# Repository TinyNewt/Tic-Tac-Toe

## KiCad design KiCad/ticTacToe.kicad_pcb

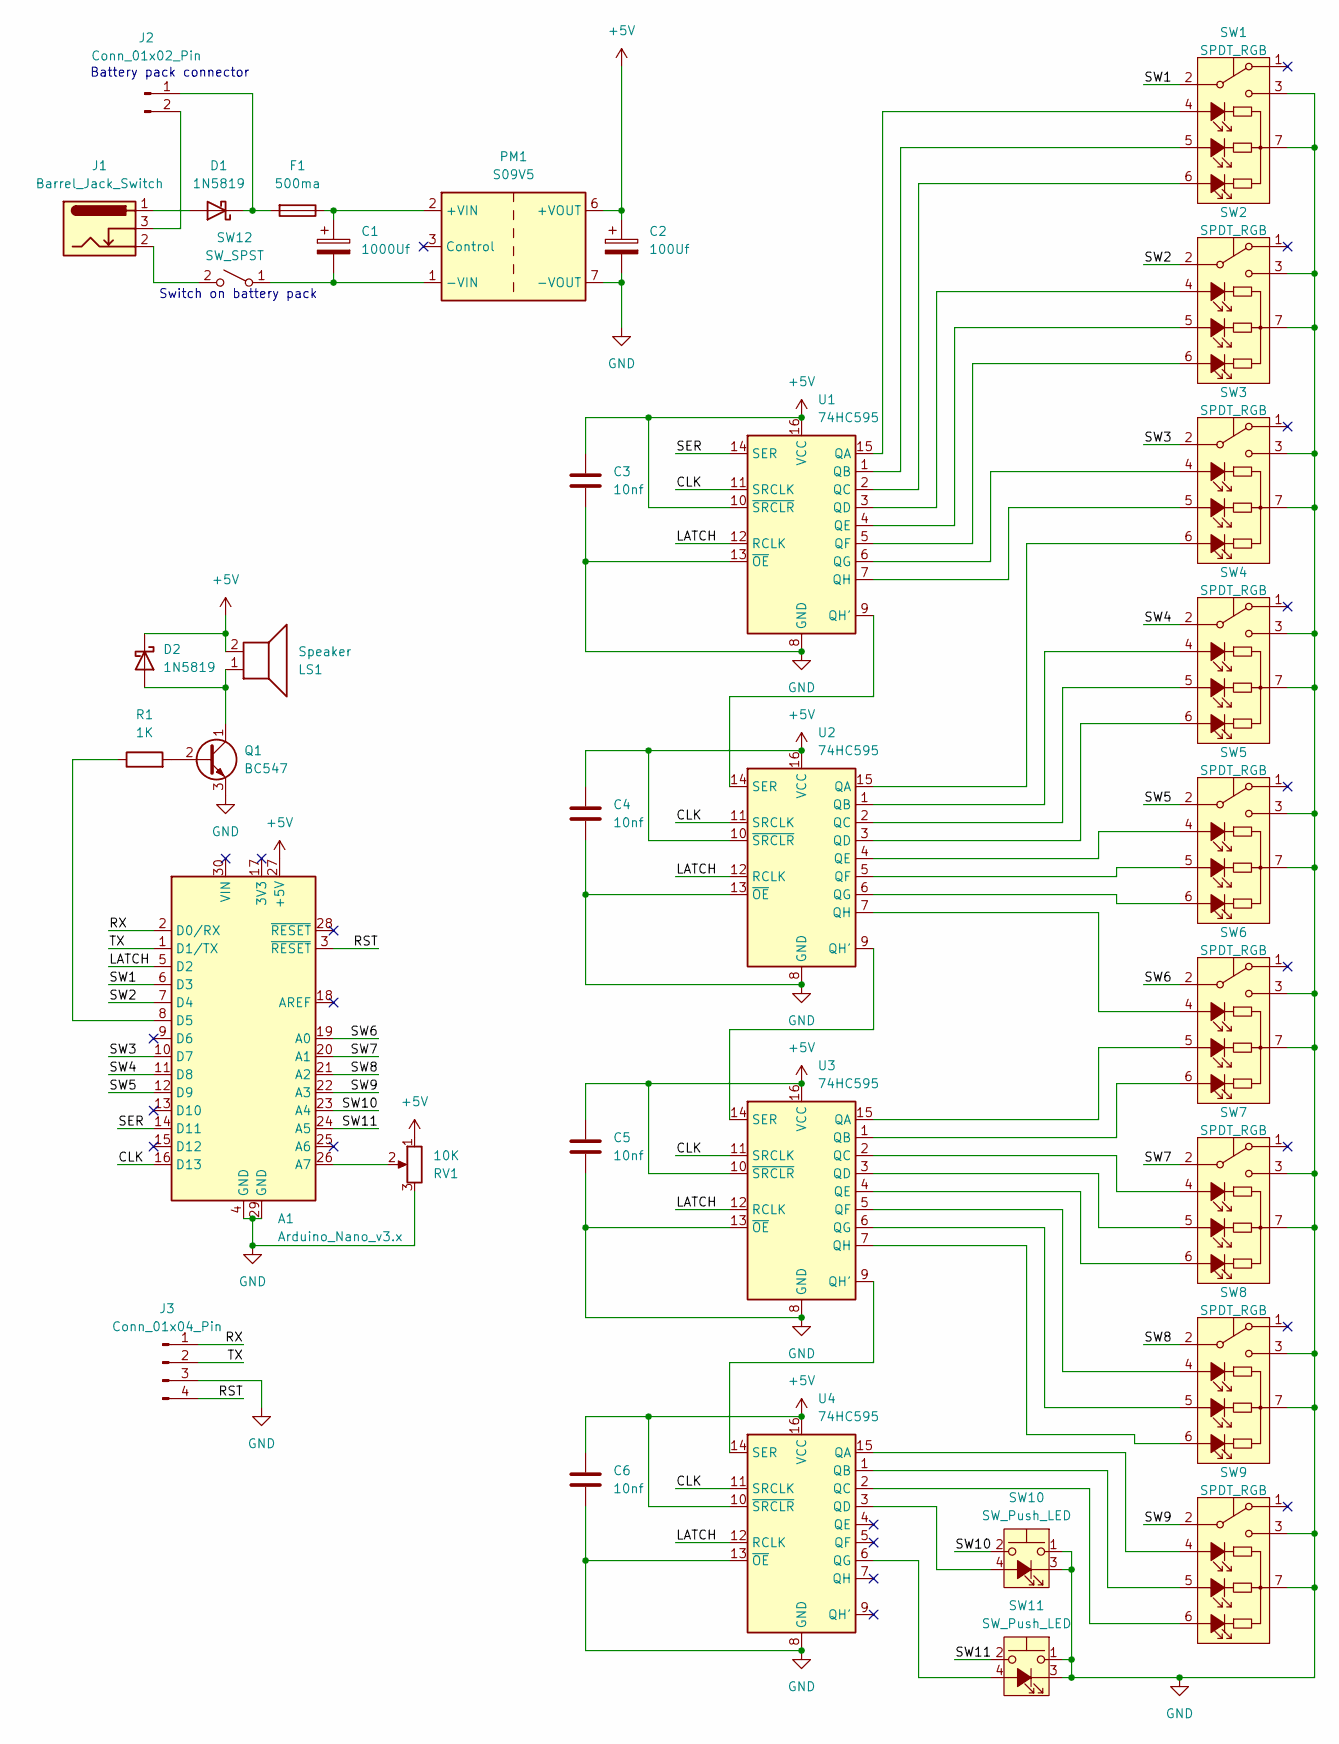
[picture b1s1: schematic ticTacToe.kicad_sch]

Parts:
A1: Arduino_Nano_v3.x; Arduino_Nano
C1: 1000Uf; CP_Radial_D8.0mm_P5.00mm; JLCPCB C10752
C2: 100Uf; CP_Radial_D8.0mm_P3.50mm; LCSC C2749
C3, C4, C5, C6: 10nf; C_Disc_D5.0mm_W2.5mm_P5.00mm
D1, D2: 1N5819; D_DO-41_SOD81_P7.62mm_Horizontal
F1: 500ma; PinHeader_1x02_P2.54mm_Vertical
J1: Barrel_Jack_Switch; BarrelJack_Horizontal
J2: Conn_01x02_Pin; PinHeader_1x02_P2.54mm_Vertical
J3: Conn_01x04_Pin; PinHeader_1x04_P2.54mm_Vertical
LS1: Speaker; PinHeader_1x02_P2.54mm_Vertical
PM1: S09V5; S09
Q1: BC547; TO-92_Inline_Wide
R1: 1K; R_Axial_DIN0204_L3.6mm_D1.6mm_P7.62mm_Horizontal
RV1: 10K; Potentiometer_Alps_RK163_Single_Horizontal
SW1, SW2, SW3, SW4, SW5, SW6, SW7, SW8, SW9: SPDT_RGB; SPDT_RGB_D19
SW10, SW11: SW_Push_LED; PinHeader_1x04_P2.54mm_Vertical
SW12: SW_SPST; PinHeader_1x02_P2.54mm_Vertical
U1, U2, U3, U4: 74HC595; DIP-16_W7.62mm_LongPads

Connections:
+5V: A1.27 (+5V), C2.1, C3.1, C4.1, C5.1, C6.1, D2.1 (K), LS1.2, PM1.6 (+VOUT), RV1.1, U1.10 (~SRCLR), U1.16 (VCC), U2.10 (~SRCLR), U2.16 (VCC), U3.10 (~SRCLR), U3.16 (VCC), U4.10 (~SRCLR), U4.16 (VCC)
/CLK: A1.16 (D13), U1.11 (SRCLK), U2.11 (SRCLK), U3.11 (SRCLK), U4.11 (SRCLK)
/LATCH: A1.5 (D2), U1.12 (RCLK), U2.12 (RCLK), U3.12 (RCLK), U4.12 (RCLK)
/RST: A1.3 (~RESET), J3.4
/RX: A1.2 (D0/RX), J3.1
/SER: A1.14 (D11), U1.14 (SER)
/SW1: A1.6 (D3), SW1.2 (B)
/SW2: A1.7 (D4), SW2.2 (B)
/SW3: A1.10 (D7), SW3.2 (B)
/SW4: A1.11 (D8), SW4.2 (B)
/SW5: A1.12 (D9), SW5.2 (B)
/SW6: A1.19 (A0), SW6.2 (B)
/SW7: A1.20 (A1), SW7.2 (B)
/SW8: A1.21 (A2), SW8.2 (B)
/SW9: A1.22 (A3), SW9.2 (B)
/SW10: A1.23 (A4), SW10.2
/SW11: A1.24 (A5), SW11.2
/TX: A1.1 (D1/TX), J3.2
GND: A1.4 (GND), A1.29 (GND), C2.2, C3.2, C4.2, C5.2, C6.2, J3.3, PM1.7 (-VOUT), Q1.3 (E), RV1.3, SW1.3 (C), SW1.7 (K), SW2.3 (C), SW2.7 (K), SW3.3 (C), SW3.7 (K), SW4.3 (C), SW4.7 (K), SW5.3 (C), SW5.7 (K), SW6.3 (C), SW6.7 (K), SW7.3 (C), SW7.7 (K), SW8.3 (C), SW8.7 (K), SW9.3 (C), SW9.7 (K), SW10.1, SW10.3 (K), SW11.1, SW11.3 (K), U1.8 (GND), U1.13 (~OE), U2.8 (GND), U2.13 (~OE), U3.8 (GND), U3.13 (~OE), U4.8 (GND), U4.13 (~OE)
unnamed: A1.26 (A7), RV1.2
unnamed: A1.8 (D5), R1.1
unnamed: D1.2 (A), J1.1
unnamed: D1.1 (K), F1.2, J2.1
unnamed: D2.2 (A), LS1.1, Q1.1 (C)
unnamed: J1.3, J2.2
unnamed: C1.1, F1.1, PM1.2 (+VIN)
unnamed: C1.2, PM1.1 (-VIN), SW12.1 (A)
unnamed: Q1.2 (B), R1.2
unnamed: SW1.5 (G), U1.1 (QB)
unnamed: SW1.4 (R), U1.15 (QA)
unnamed: SW2.5 (G), U1.4 (QE)
unnamed: SW2.4 (R), U1.3 (QD)
unnamed: SW3.5 (G), U1.7 (QH)
unnamed: SW3.4 (R), U1.6 (QG)
unnamed: SW4.5 (G), U2.2 (QC)
unnamed: SW4.4 (R), U2.1 (QB)
unnamed: SW5.5 (G), U2.5 (QF)
unnamed: SW5.4 (R), U2.4 (QE)
unnamed: SW6.5 (G), U3.15 (QA)
unnamed: SW6.4 (R), U2.7 (QH)
unnamed: SW7.5 (G), U3.3 (QD)
unnamed: SW7.4 (R), U3.2 (QC)
unnamed: SW8.5 (G), U3.6 (QG)
unnamed: SW8.4 (R), U3.5 (QF)
unnamed: SW9.5 (G), U4.1 (QB)
unnamed: SW9.4 (R), U4.15 (QA)
unnamed: SW10.4 (A), U4.3 (QD)
unnamed: SW11.4 (A), U4.6 (QG)
unnamed: J1.2, SW12.2 (B)
unnamed: SW1.6 (B), U1.2 (QC)
unnamed: SW2.6 (B), U1.5 (QF)
unnamed: U1.9 (QH'), U2.14 (SER)
unnamed: SW3.6 (B), U2.15 (QA)
unnamed: SW4.6 (B), U2.3 (QD)
unnamed: SW5.6 (B), U2.6 (QG)
unnamed: U2.9 (QH'), U3.14 (SER)
unnamed: SW6.6 (B), U3.1 (QB)
unnamed: SW7.6 (B), U3.4 (QE)
unnamed: U3.9 (QH'), U4.14 (SER)
unnamed: SW8.6 (B), U3.7 (QH)
unnamed: SW9.6 (B), U4.2 (QC)

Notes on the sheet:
Battery pack connector
Switch on battery pack

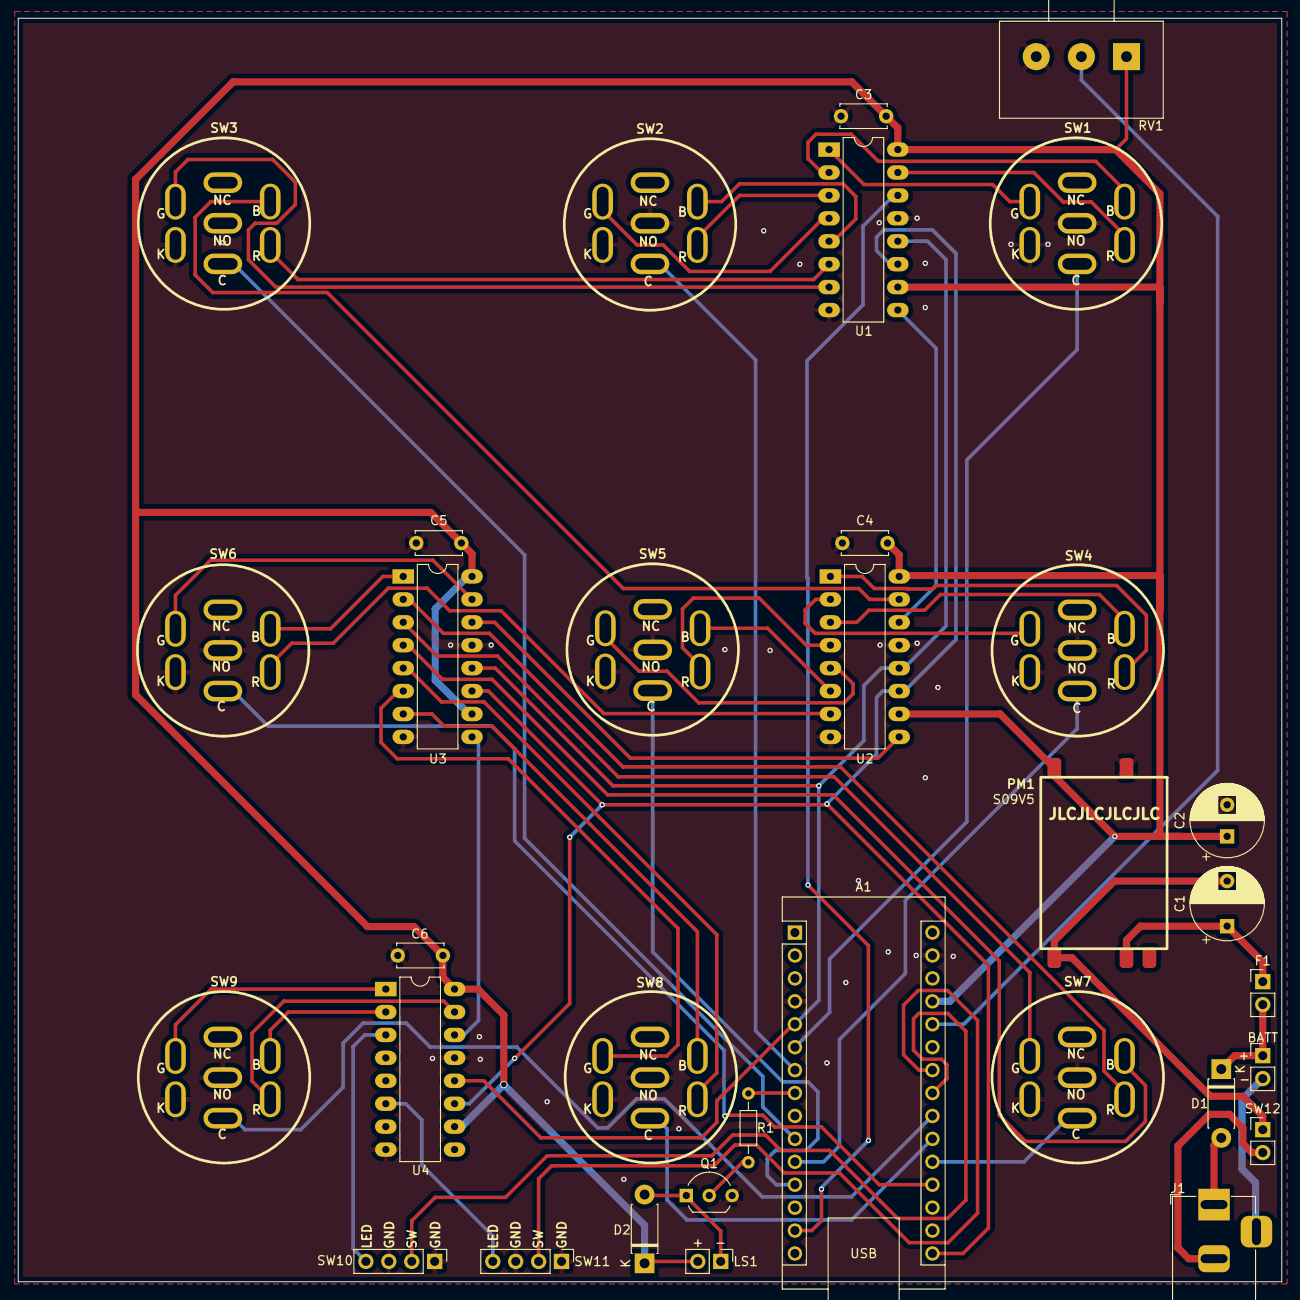
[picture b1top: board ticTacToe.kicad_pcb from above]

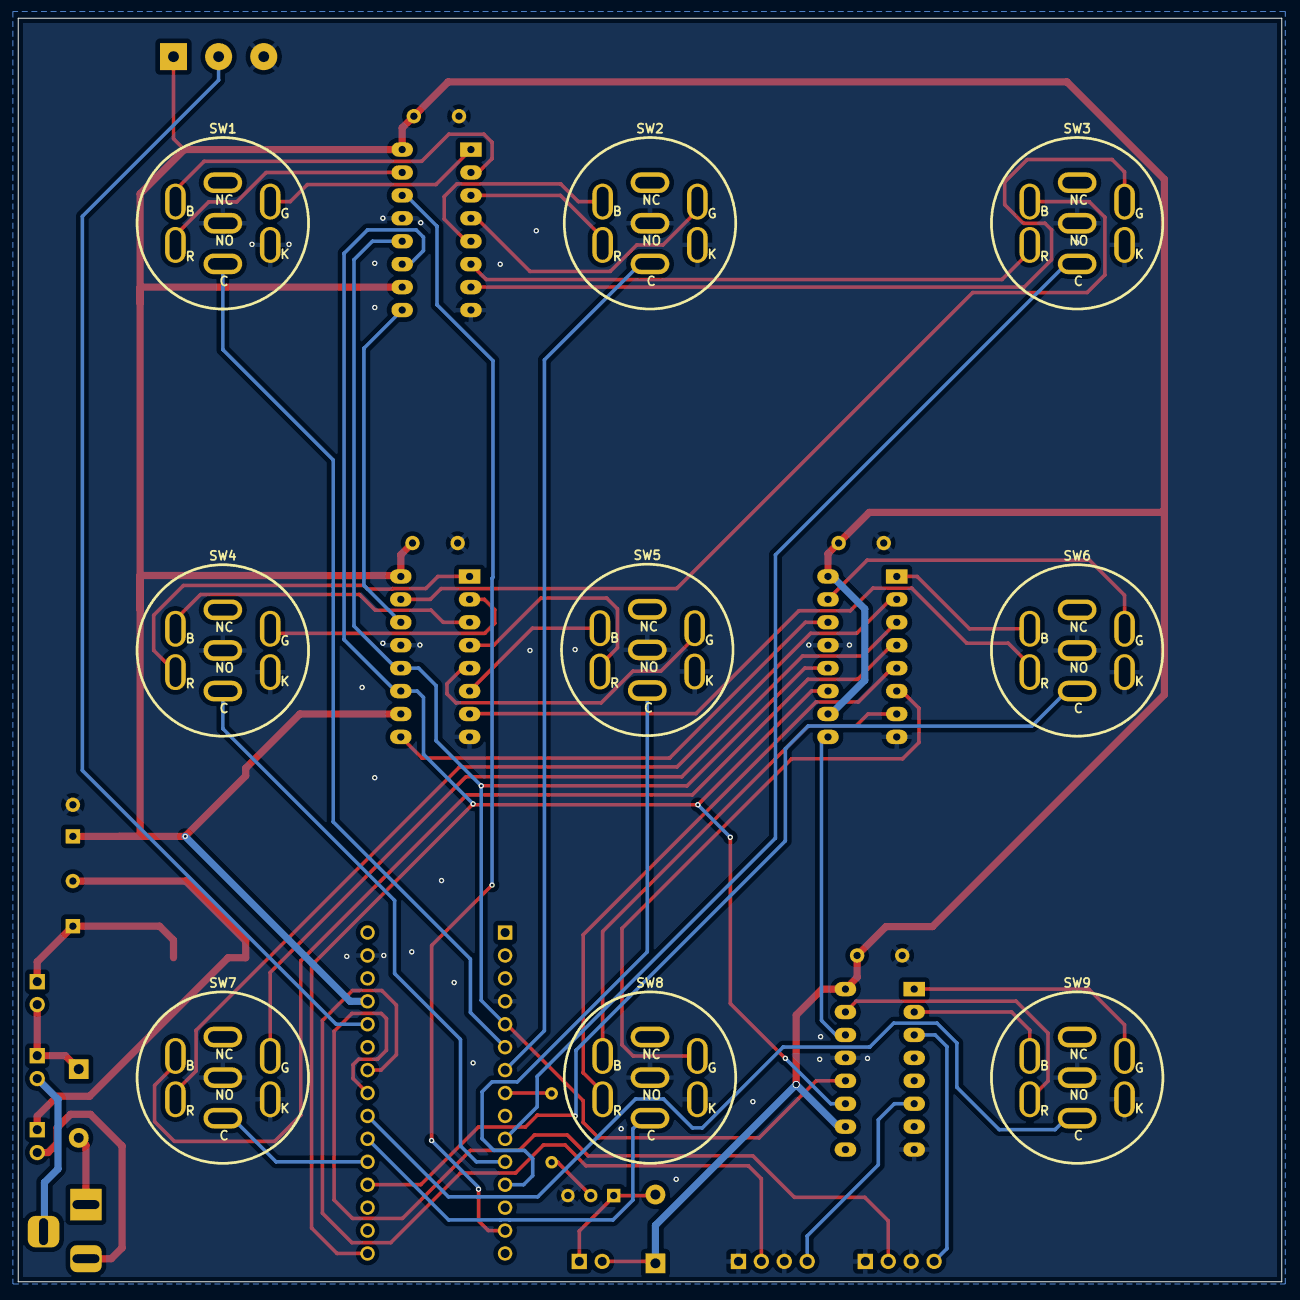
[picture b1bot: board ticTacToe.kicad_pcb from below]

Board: 2 copper layers, 140.0 x 140.0 mm, 33 parts (9 on the bottom side), 58 nets.

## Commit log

2025-01-27 Add schematic and sketch
2025-01-27 Add svg format for the schematic
2025-01-27 Added speaker to the schematic
2025-01-27 Create a pcb to make building easier
2025-01-27 Add sound effects to the arduino sketch
2025-01-27 Update the schematic svg
2025-01-27 Added 3d pot
2025-01-27 Added 3d object to foortprint
2025-01-27 Added push button render and board render examples
